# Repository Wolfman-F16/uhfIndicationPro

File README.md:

# UHF Indication Board Pro
This board and firmware can be used standalone or with the UHF Control Board RP.
The full potential is, of course, unlocked with the UHF Control Board RP.

The board can be communicated with using SPI, UART or I2C (not implemented).

# AVR Fuse Bits
Use your ISP programmer of choice to set the fuse bits of the ATmega8 microcontroller. ATTENTION: the pinout of the board is not standard! Make sure you have a modified ribbon cable or use jumper wires to make the appropriate connections!

    avrdude -c <programmer> -p m8 -Ulfuse:v:0xfe:m -Uhfuse:v:0xd1:m

# Flashing Firmware

    avrdude -c <programmer> -p m8 -Uflash:v:UhfIndicationPro.<version>.hex

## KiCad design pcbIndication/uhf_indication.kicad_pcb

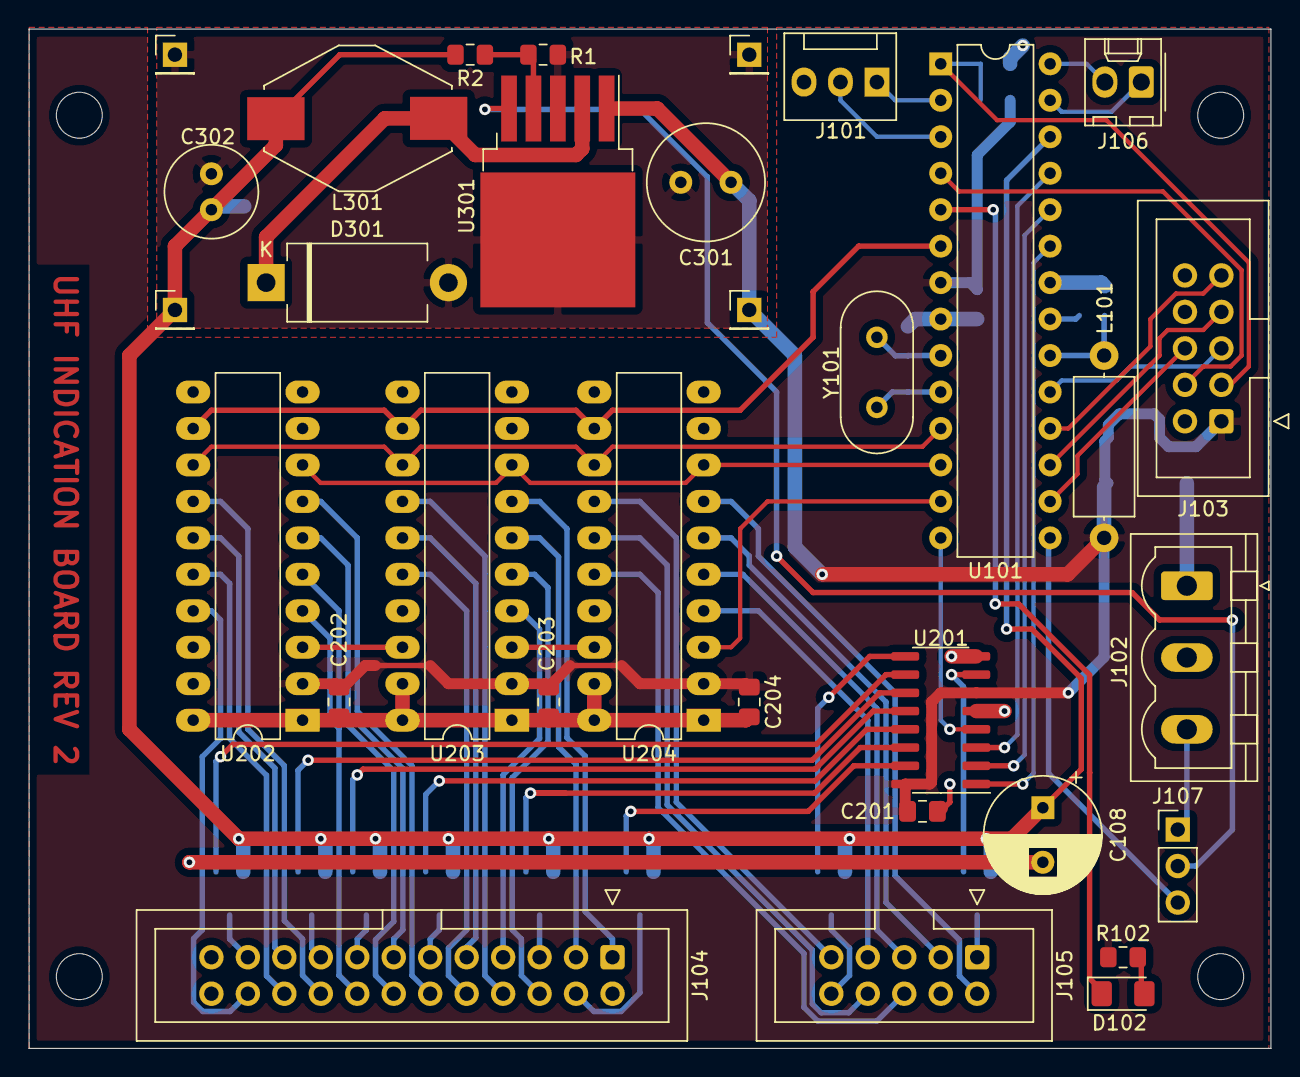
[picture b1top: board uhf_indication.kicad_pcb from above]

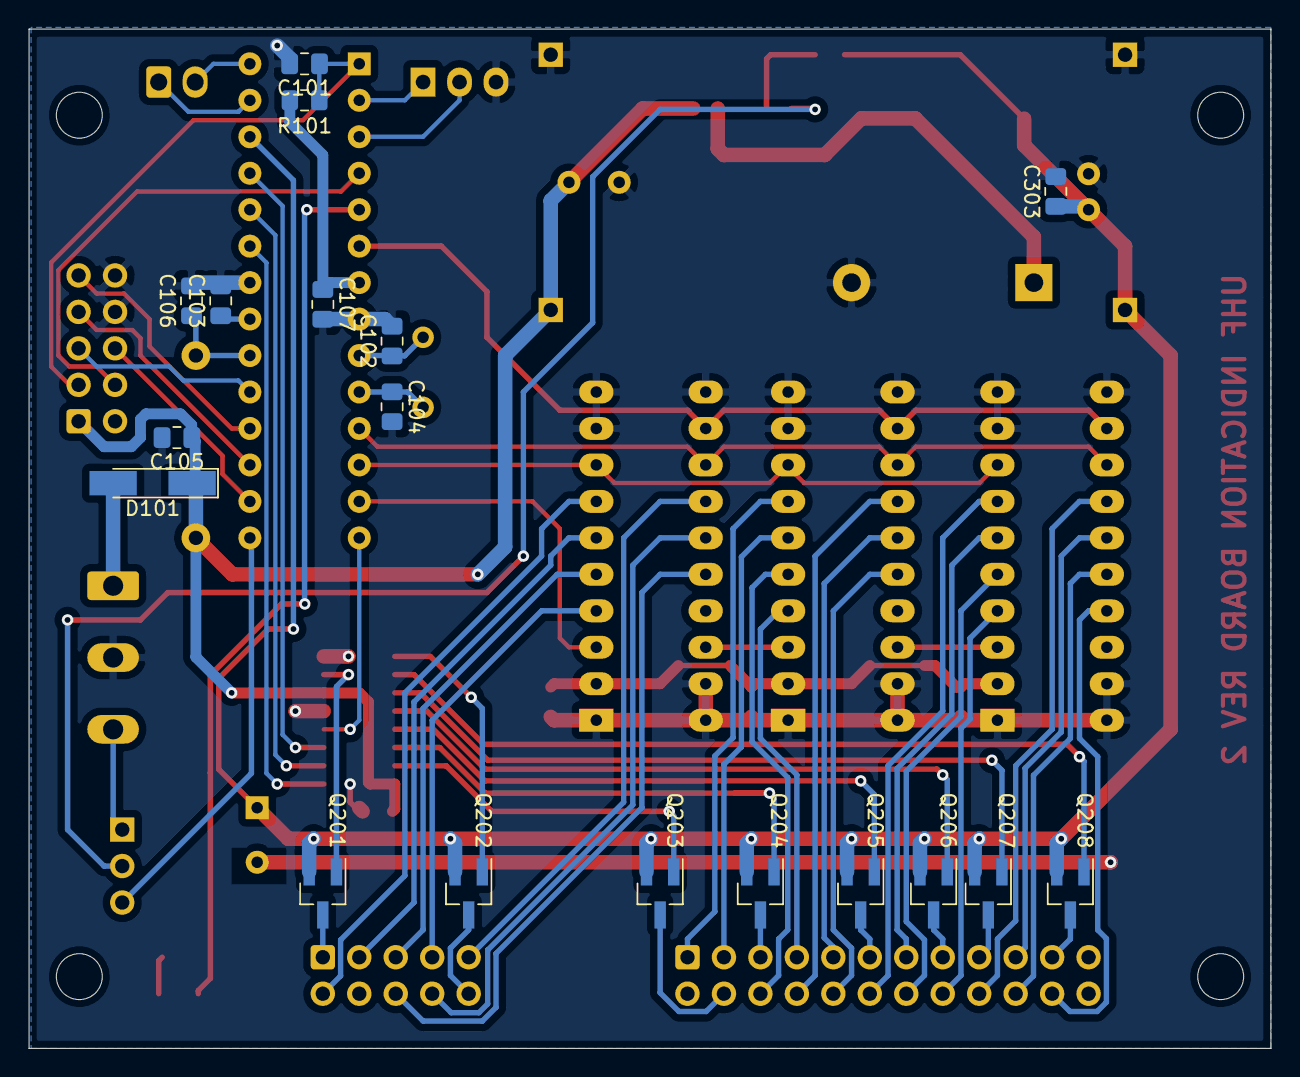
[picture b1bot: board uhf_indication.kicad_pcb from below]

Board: 2 copper layers, 86.5 x 71.0 mm, 54 parts (18 on the bottom side), 73 nets.

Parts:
C101, C103, C303: 10nF; C_0805_2012Metric_Pad1.18x1.45mm_HandSolder
C102, C104: 22p; C_0805_2012Metric_Pad1.18x1.45mm_HandSolder
C105, C106: 100pF; C_0805_2012Metric_Pad1.18x1.45mm_HandSolder
C107, C201, C202, C203, C204: 100nF; C_0805_2012Metric_Pad1.18x1.45mm_HandSolder
C108: 2.2uF; CP_Radial_D8.0mm_P3.80mm
C301: 470uF; C_Radial_D8.0mm_H7.0mm_P3.50mm
C302: 220uF; C_Radial_D6.3mm_H5.0mm_P2.50mm
D101: 2A SMD Fuse; D_MiniMELF_Handsoldering
D102: Green LED; LED_1206_3216Metric_Pad1.42x1.75mm_HandSolder
D301: 1N5825; D_DO-201_P12.70mm_Horizontal
H101, H102, H103, H104: MountingHole; MountingHole_3.2mm_M3
J101: UART; FanPinHeader_1x03_P2.54mm_Vertical
J102: Power; PhoenixContact_MSTBVA_2,5_3-G_1x03_P5.00mm_Vertical
J103: COMM; IDC-Header_2x05_P2.54mm_Vertical
J104: Frequency; IDC-Header_2x12_P2.54mm_Vertical
J105: Channel; IDC-Header_2x05_P2.54mm_Vertical
J106: I2C; Molex_KK-254_AE-6410-02A_1x02_P2.54mm_Vertical
J107: Power Control Select; PinHeader_1x03_P2.54mm_Vertical
J301: PWR_IN_P; PinHeader_1x01_P2.54mm_Vertical
J302: PWR_IN_GND; PinHeader_1x01_P2.54mm_Vertical
J303: PWR_OUT_P; PinHeader_1x01_P2.54mm_Vertical
J304: PWR_OUT_GND; PinHeader_1x01_P2.54mm_Vertical
L101: 10uH; L_Axial_L9.5mm_D4.0mm_P12.70mm_Horizontal_Fastron_SMCC
L301: 47uH; L_Fastron_PISN_Handsoldering
Q201, Q202, Q203, Q204, Q205, Q206, Q207, Q208: TSM2301ACX; SOT-23_Handsoldering
R1: 3k3; R_0805_2012Metric_Pad1.15x1.40mm_HandSolder
R2: 4k7; R_0805_2012Metric_Pad1.15x1.40mm_HandSolder
R101: 8k2; R_0805_2012Metric_Pad1.15x1.40mm_HandSolder
R102: 470R; R_0805_2012Metric_Pad1.15x1.40mm_HandSolder
U101: ATmega8-16PU; DIP-28_W7.62mm
U201: 74HC137; SOIC-16_3.9x9.9mm_P1.27mm
U202, U203, U204: TPIC6595; DIP-20_W7.62mm_LongPads
U301: LM2596S-ADJ; TO-263-5_TabPin3
Y101: 16 MHz; Crystal_HC49-U_Vertical

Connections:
+3V0: C108.1, C302.1, C303.1, J303.1, L301.2, Q201.2, Q202.2, Q203.2, Q204.2, Q205.2, Q206.2, Q207.2, Q208.2, R2.1, U101.26
/ADDR0: U101.23, U201.1
/ADDR1: U101.24, U201.2
/ADDR2: U101.25, U201.3
/AREF: C103.1, U101.21
/AVCC: C106.1, L101.1, U101.20
/D7_A: J105.6, U204.16
/D7_B: J105.3, U204.6
/D7_C: J105.5, U204.5
/D7_D: J105.9, U204.14
/D7_E: J105.7, U204.4
/D7_F: J105.8, U204.15
/D7_G: J105.2, U204.7
/D7_N1: J105.1, Q201.3
/D7_N2: J105.10, Q202.3
/D14_A: J104.9, U203.15
/D14_B: J104.13, U202.6
/D14_C: J104.6, U203.5
/D14_D: J104.8, U203.14
/D14_Dp: J104.10, U203.16
/D14_E: J104.12, U202.7
/D14_F: J104.7, U203.4
/D14_G1: J104.22, U202.17
/D14_G2: J104.20, U202.16
/D14_H: J104.1, U203.7
/D14_J: J104.3, U203.6
/D14_K: J104.19, U202.15
/D14_L: J104.18, U202.14
/D14_M: J104.16, U202.4
/D14_N: J104.14, U202.5
/Display Control/C01: Q202.1, U201.9
/Display Control/C10: Q201.1, U201.7
/Display Control/F1: Q203.1, U201.15
/Display Control/F2: Q204.1, U201.14
/Display Control/F3: Q205.1, U201.13
/Display Control/F4: Q206.1, U201.12
/Display Control/F5: Q207.1, U201.11
/Display Control/F6: Q208.1, U201.10
/I2C_SCL: J106.2, U101.28
/I2C_SDA: J106.1, U101.27
/MISO: J103.9, U101.18
/MOSI: J103.7, U101.17
/N1: J104.4, Q203.3
/N2: J104.5, Q204.3
/N3: J104.11, Q205.3
/N4: J104.15, Q206.3
/N5: J104.17, Q207.3
/N6: J104.21, Q208.3
/PWR_ENA: J107.2, U301.5
/PWR_ENA_EXT: J102.3, J107.1
/RX: J101.1, U101.2
/SCK: J103.5, U101.19
/SHF_RCK: U101.6, U202.12, U203.12, U204.12
/SHF_SCK: U101.11, U202.13, U203.13, U204.13
/SHF_SDA: U101.13, U204.3
/TRIGGER: J103.4, U101.4
/TX: J101.2, U101.3
/XTAL1: C102.1, U101.9, Y101.1
/XTAL2: C104.1, U101.10, Y101.2
/~MUX_ENA: U101.14, U201.4
/~RESET: C101.1, J103.3, R101.2, U101.1
/~SHF_CLR: U101.12, U202.8, U203.8, U204.8
/~SS: J103.6, U101.16
/~STATUS_LED: D102.1, U101.5
GND: C101.2, C102.2, C103.2, C104.2, C105.2, C106.2, C107.2, C108.2, C201.2, C202.2, C203.2, C204.2, C301.2, C302.2, C303.2, D301.2, J101.3, J102.2, J103.8, J103.10, J302.1, J304.1, R1.2, U101.8, U101.22, U201.5, U201.8, U202.1, U202.9, U202.10, U202.11, U202.19, U202.20, U203.1, U203.9, U203.10, U203.11, U203.19, U203.20, U204.1, U204.9, U204.10, U204.11, U204.19, U204.20, U301.3
unnamed: D101.2, J102.1
unnamed: D102.2, R102.2
unnamed: D301.1, L301.1, U301.2
unnamed: J107.3, U101.15
unnamed: R1.1, R2.2, U301.4
unnamed: U202.3, U203.18
unnamed: U203.3, U204.18
VCC: C105.1, C107.1, C201.1, C202.1, C203.1, C204.1, C301.1, D101.1, J103.1, J301.1, L101.2, R101.1, R102.1, U101.7, U201.6, U201.16, U202.2, U203.2, U204.2, U301.1

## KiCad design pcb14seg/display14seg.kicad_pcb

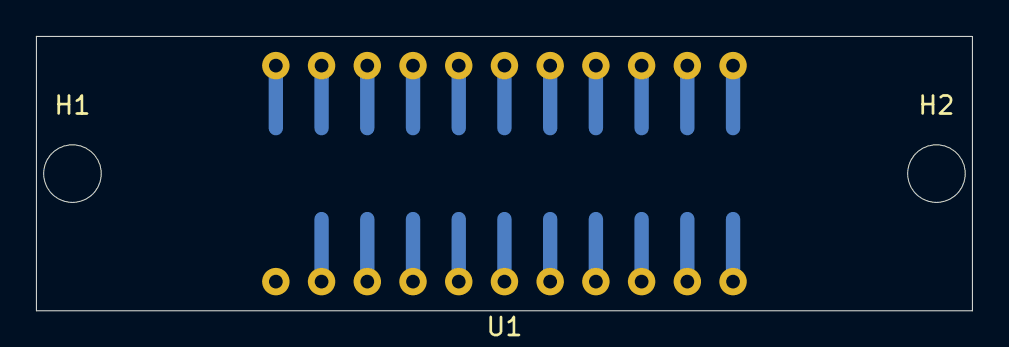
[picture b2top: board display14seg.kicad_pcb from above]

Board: 2 copper layers, 52.0 x 15.2 mm, 4 parts (1 on the bottom side), 21 nets.

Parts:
H1, H2: MountingHole; MountingHole_3.2mm_M3_DIN965
J1: Conn_02x11_Odd_Even; PinHeader_2x11_P2.54mm_Vertical_SMD
U1: D60401CS

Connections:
/N1: J1.4, U1.2
/N2: J1.5, U1.20
/N3: J1.11, U1.17
/N4: J1.15, U1.15
/N5: J1.17, U1.14
/N6: J1.21, U1.12
/P1: J1.9, U1.18
/P2: J1.13, U1.16
/P3: J1.6, U1.3
/P4: J1.8, U1.4
/P5: J1.12, U1.6
/P6: J1.7, U1.19
/P7: J1.22, U1.11
/P8: J1.20, U1.10
/P9: J1.1, U1.22
/P10: J1.3, U1.21
/P11: J1.19, U1.13
/P12: J1.18, U1.9
/P13: J1.16, U1.8
/P14: J1.14, U1.7
/P15: J1.10, U1.5

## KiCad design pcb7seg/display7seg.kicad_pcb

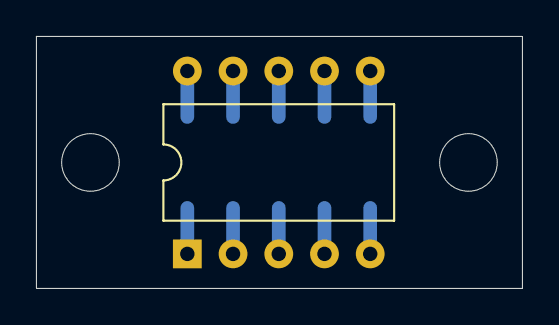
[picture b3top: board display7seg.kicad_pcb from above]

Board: 2 copper layers, 27.0 x 14.0 mm, 4 parts (1 on the bottom side), 10 nets.

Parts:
H101, H102: MountingHole; MountingHole_3.2mm_M3_DIN965
J1: SMD Conn; PinHeader_2x05_P2.54mm_Vertical_SMD
U1: CL03621A; DIP-10_W10.16mm

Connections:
/PIN_1: J1.9, U1.1
/PIN_2: J1.7, U1.2
/PIN_3: J1.5, U1.3
/PIN_4: J1.3, U1.4
/PIN_5: J1.1, U1.5
/PIN_6: J1.2, U1.6
/PIN_7: J1.4, U1.7
/PIN_8: J1.6, U1.8
/PIN_9: J1.8, U1.9
/PIN_10: J1.10, U1.10

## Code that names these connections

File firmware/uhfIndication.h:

/*
 * UHFIndication.h
 *
 *  Created on: 30.01.2010
 *      Author: Wolfman
 */

#ifndef UHFINDICATION_H_
#define UHFINDICATION_H_

#include "adc.h"
#include "spi.h"

#include <avr/io.h>
#include <stdint.h>

#define _DEBUG_ 0

#ifndef EEMEM
#define EEMEM  __attribute__ ((section (".eeprom")))
#endif

#define BEGIN_INFINITE_LOOP for(;;) {
#define END_INFINITE_LOOP   }

#define TRUE            1
#define FALSE           0

/*----------------------------------------------------------------------------*/
// I/O
/*----------------------------------------------------------------------------*/
#define PORT_OUT_SHFT   PORTD

#define PIN_SHFT_RCK    PORTD4
#define PIN_SHFT_DAT    PORTD7
#define PIN_SHFT_SCK    PORTD5
#define PIN_SHFT_CLR    PORTD6

#define PORT_OUT_MUX_ENA    PORTB
#define PIN_MUX_ENA         PORTB0

#define PORT_OUT_MUX    PORTC
#define PIN_MUX_ADDR0   PORTC0
#define PIN_MUX_ADDR1   PORTC1
#define PIN_MUX_ADDR2   PORTC2
#define PORT_MUX_MASK   0x07


#define PORT_LED        PORTD
#define PIN_STATUS_LED  PORTD3

#define PORT_OUT_PWM    PORTB
#define PIN_PWM         PORTB1

#define PIN_TRIGGER     PORTD2

#define PIN_SPI_CLK     PORTB5
#define PIN_SPI_MISO    PORTB4
#define PIN_SPI_MOSI    PORTB3
#define PIN_SPI_SS      PORTB2
#define PIN_RX          PORTD0
#define PIN_TX          PORTD1

/*----------------------------------------------------------------------------*/
// UHF
/*----------------------------------------------------------------------------*/
// reserve mem for partial ASCII table
#define MAX_BYTE        0x5A
#define CHANNEL_LENGTH  2
#define FREQ_LENGTH     6
#define BYTE_LENGTH     8

#define CHANNEL_OFFSET  7
/* 7 seg displays*/
#define BLANK_DIGIT     0xFF
#define TEST_DIGIT      ~0x7F
#define DECIMAL_POINT   0x80
/* 14 seg displays */
#define BLANK16_DIGIT   0xFFFF
#define TEST16_DIGIT    0x0040
#define DECIMAL16_POINT 0x0040

/*----------------------------------------------------------------------------*/
// UART
/*----------------------------------------------------------------------------*/
// parser
#define NEWLINE         '\r'
#define NEWPAGE         0x0C
#define BACKSPACE       0x7F
#define TERMINATOR      0x00

#define MAX_BUFFER_SIZE 20
#define MAX_MSG_LENGTH  25
#define MAX_MESSAGES    9
#define MAX_COMMANDS    5
// error codes for TTYFlag (number specifies bit)
#define ERROR_OK        0
#define ERROR_BUFFER    1
#define ERROR_CMD       2
#define ERROR_PARAM     3
// commands
#define CMD_B           1
#define CMD_C           2
#define CMD_D           3
#define CMD_F           4
#define CMD_INFO        5

/*----------------------------------------------------------------------------*/
// SPI
/*----------------------------------------------------------------------------*/
//indicates start of frame
#define MSG_TYPE        0x1A
// for channel & frequency for starters.
#define MAX_SPI_BUFFER  8

/*----------------------------------------------------------------------------*/
// SW Timer
/*----------------------------------------------------------------------------*/
#define SWT_ADC_ISR     0
#define SWT_TEST_ISR    1
#define SWT_CHARLIE_ISR 2

/****************************   Structures      *******************************/
typedef struct {
  uint8_t channelString[CHANNEL_LENGTH];
  uint8_t frequencyString[FREQ_LENGTH];
  uint8_t brightnessDay;
  uint8_t brightnessNight;
  uint8_t day;
  uint8_t version;
} radio_t;


typedef struct {
  unsigned boot:1;
  unsigned updateAdc:1;
  unsigned updateTimer:1;
  unsigned updateDisplay:1;
  unsigned currFrequency:3;
  unsigned currChannel:1;
} status_t;

/****************************   Variables       *******************************/
volatile radio_t radio;
volatile status_t status;
volatile uint8_t currentAdcValue;

extern uint8_t asciiTable[128];
extern uint8_t table[] EEMEM;

extern volatile uint8_t swTimer[3];

/****************************   FUNCTION DECLARATIONS ************************/
void initIO(void);
void setDefaults(void);

void updateDisplay(void);

void setLightTestOn(void);
void setLightTestOff(void);
void setLightBlank(void);

/****************************   INLINE FUNCTIONS    **************************/
/*
 * sets status led off
 */
static inline void setStatusLedOff()
{
  PORT_LED |= _BV(PIN_STATUS_LED);
}

/*
 * sets status led on
 */
static inline void setStatusLedOn()
{
  PORT_LED &= ~_BV(PIN_STATUS_LED);
}

/*
 * set charlie plexing address
 */
static inline void charlieplex(uint8_t index)
{
  PORTC &= ~PORT_MUX_MASK;
  PORTC |= index & PORT_MUX_MASK;
}

/**************************** Interrupt Service Routine     ******************/
/**
 * interrupt service routine
 *
 * Display test
 */
static inline void isrTestTimer()
{
  static uint8_t timer0Ext = 0x2F;

  if(timer0Ext > 0) {
    timer0Ext--;
  } else {
    // notify main loop
    status.updateTimer = TRUE;
  }
}

/**
 * interrupt service routine
 *
 * ADC conversion
 */
static inline void isrAdc()
{
  startAdcConversion();
}

/**
 * interrupt service routine
 *
 * charlie plexing
 */
static inline void isrCharlieplex()
{
  if (swTimer[SWT_CHARLIE_ISR] == 0) {
    swTimer[SWT_CHARLIE_ISR] = 8;
    charlieplex(CHANNEL_OFFSET - status.currChannel);
    status.currChannel++;
    if (status.currChannel >= CHANNEL_LENGTH) {
      status.currChannel = 0;
    }
  } else {
    swTimer[SWT_CHARLIE_ISR]--;
    charlieplex(status.currFrequency);
    status.currFrequency++;
    if (status.currFrequency >= FREQ_LENGTH) {
      status.currFrequency = 0;
    }
  }
  status.updateDisplay = 1;
}



/**/
/**
 * interrupt service routine
 *
 * SPI communication
 */
static inline void isrSpi(void)
{
  static uint8_t radioIndex = 0;
  uint8_t *radioArray = (uint8_t*)& radio;

  spiRxValue = SPDR;
  /* debug */
  UDR = spiRxValue;
  /* debug */
  if(spiRxValue == SPI_SOF) {
    radioIndex = 0;
    setStatusLedOn();
    return;
  }
  if(radioIndex < (CHANNEL_LENGTH + FREQ_LENGTH)) {
    if(spiRxValue == ' ') {
      spiRxValue = 'X';  // whitespace conversion
    }
    radioArray[radioIndex++] = spiRxValue;
  }
}
#endif /* UHFINDICATION_H_ */
